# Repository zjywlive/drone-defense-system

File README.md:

# IMPORTANT: This repository has moved to https://git.stephendownward.ca/laptopdude90/drone-defense-system

This is a system that I have created from scratch. The idea is to detect drones with an Xbox Kinect and then take them down with a weapon that has yet to be decided. The full article can be read here: http://www.stephendownward.ca/2015/12/shooting-down-drones-with-the-kinect/ 

Currently, I am going through the process of redesigning the hardware from scratch. Instead of Nema 23s and beefy stepper motors, I am switching to Nema 17s and regular A4983 stepper drivers. I have also designed a custom board for it. This means that the STL files are incomplete, and printing them will result in something that won't work. I am currently between 3D printers, and I can't add in the second set screw mount until I confirm the first one works. 

TODO:

-Port Kinect/C# code to Raspberry Pi

-Finish STL model

-Finish controller board - Remove Arduino altogether and make it Pi Hat?

-Make build guide

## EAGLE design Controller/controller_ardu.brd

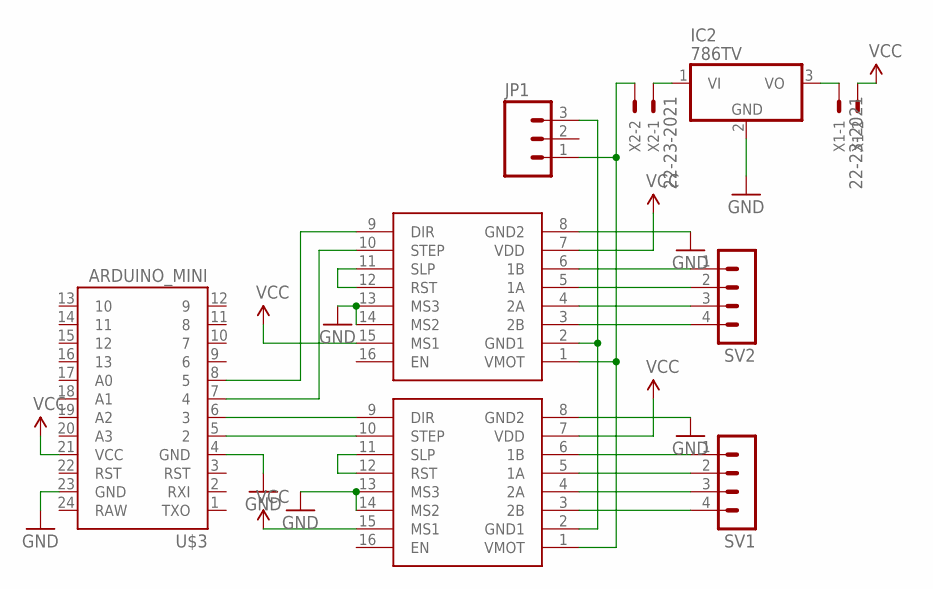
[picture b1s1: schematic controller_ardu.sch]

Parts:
IC2: 786TV; TO220V
JP1: M03SCREW; SCREWTERMINAL-3.5MM-3
SV1, SV2: MA04-1
U$1, U$2: POLOLUESTEPPERDRIVER; DIL16
U$3: ARDUINO_MINI
X1, X2: 22-23-2021

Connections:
GND: IC2.2 (GND), U$1.8 (GND2), U$1.13 (MS3), U$1.14 (MS2), U$2.8 (GND2), U$2.13 (MS3), U$2.14 (MS2), U$3.4 (GND), U$3.23 (GND)
unnamed: SV2.1, U$2.6 (1B)
unnamed: SV2.2, U$2.5 (1A)
unnamed: SV2.3, U$2.4 (2A)
unnamed: SV2.4, U$2.3 (2B)
unnamed: U$2.10 (STEP), U$3.7 (4)
unnamed: U$2.9 (DIR), U$3.8 (5)
unnamed: U$2.11 (SLP), U$2.12 (RST)
unnamed: SV1.1, U$1.6 (1B)
unnamed: SV1.2, U$1.5 (1A)
unnamed: SV1.3, U$1.4 (2A)
unnamed: SV1.4, U$1.3 (2B)
unnamed: U$1.9 (DIR), U$3.6 (3)
unnamed: U$1.10 (STEP), U$3.5 (2)
unnamed: U$1.11 (SLP), U$1.12 (RST)
unnamed: JP1.3, U$1.2 (GND1), U$2.2 (GND1)
unnamed: JP1.1, U$1.1 (VMOT), U$2.1 (VMOT), X2.2
unnamed: IC2.3 (VO), X1.1
unnamed: IC2.1 (VI), X2.1
VCC: U$1.7 (VDD), U$1.15 (MS1), U$2.7 (VDD), U$2.15 (MS1), U$3.21 (VCC), X1.2

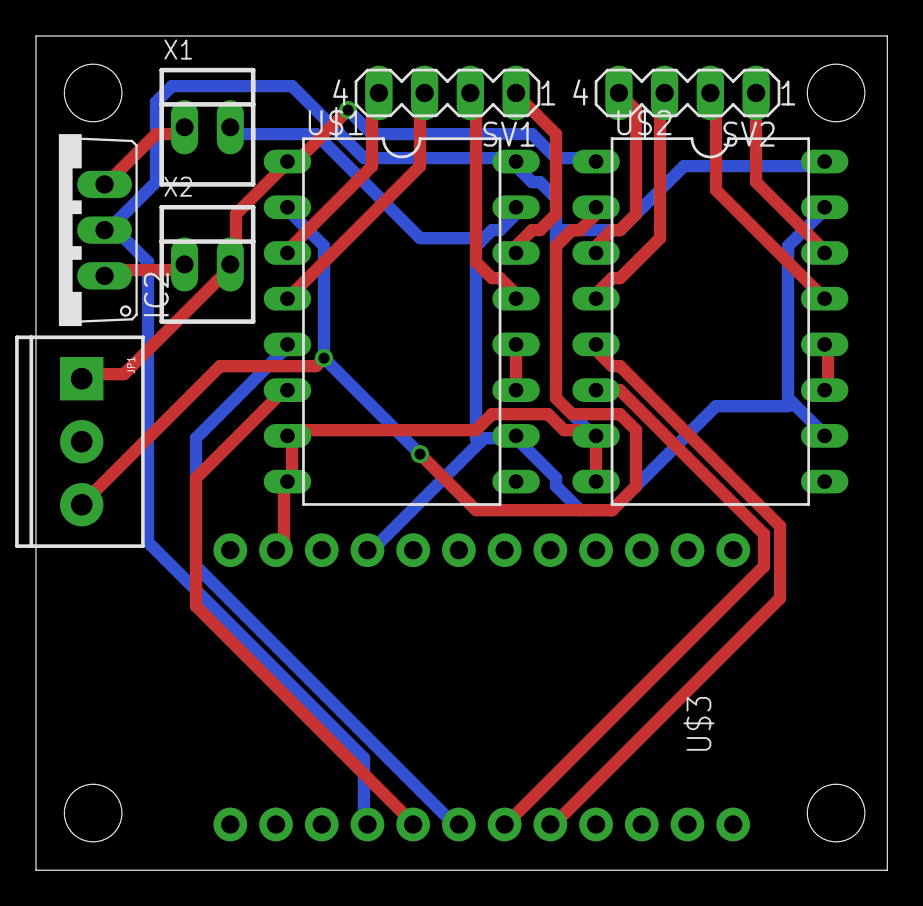
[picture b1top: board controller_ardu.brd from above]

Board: 2 copper layers, 47.3 x 46.3 mm, 9 parts (0 on the bottom side), 20 nets.

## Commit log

2015-12-28 added base files
2015-12-28 Added controllers
2016-01-06 Updated model and STLs
2016-01-06 Updated model - Adjusted tolerances
2016-01-06 Updated tolerences on the Nema shaft converter

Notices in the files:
parts and their libraries:
SparkFun-Connectors: Licensing: Creative Commons ShareAlike 4.0 International - https://creativecommons.org/licenses/by-sa/4.0
